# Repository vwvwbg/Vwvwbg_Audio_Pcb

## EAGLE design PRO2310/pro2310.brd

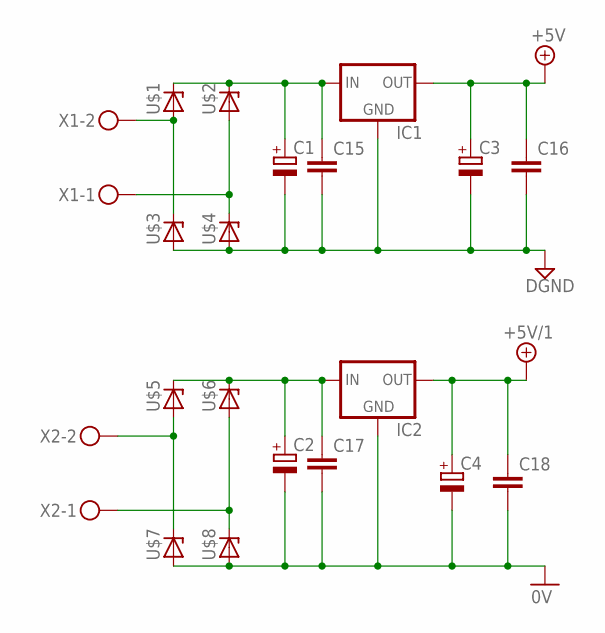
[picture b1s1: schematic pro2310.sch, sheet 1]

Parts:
C1, C2: CPOL-EUE5-10.5; E5-10,5
C3, C4: CPOL-EUE3.5-8; E3,5-8
C15, C16, C17, C18: C-EU050-055X075; C050-055X075
IC1: 78LXX
IC2: 78MXXL
U$1, U$2, U$3, U$4, U$5, U$6, U$7, U$8: 1N4148-V; 1N4148
X1, X2: MKDSN1,5/2-5,08

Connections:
0V: C2.-, C4.-, C17.2, C18.2, IC2.GND, U$7.A, U$8.A; also elsewhere on the board
+5V: C3.+, C16.1, IC1.OUT; also elsewhere on the board
+5V/1: C4.+, C18.1, IC2.OUT; also elsewhere on the board
DGND: C1.-, C3.-, C15.2, C16.2, IC1.GND, U$3.A, U$4.A; also elsewhere on the board
unnamed: C1.+, C15.1, IC1.IN, U$1.C, U$2.C
unnamed: U$5.A, U$7.C, X2.2
unnamed: U$6.A, U$8.C, X2.1
unnamed: U$2.A, U$4.C, X1.1
unnamed: C2.+, C17.1, IC2.IN, U$5.C, U$6.C
unnamed: U$1.A, U$3.C, X1.2

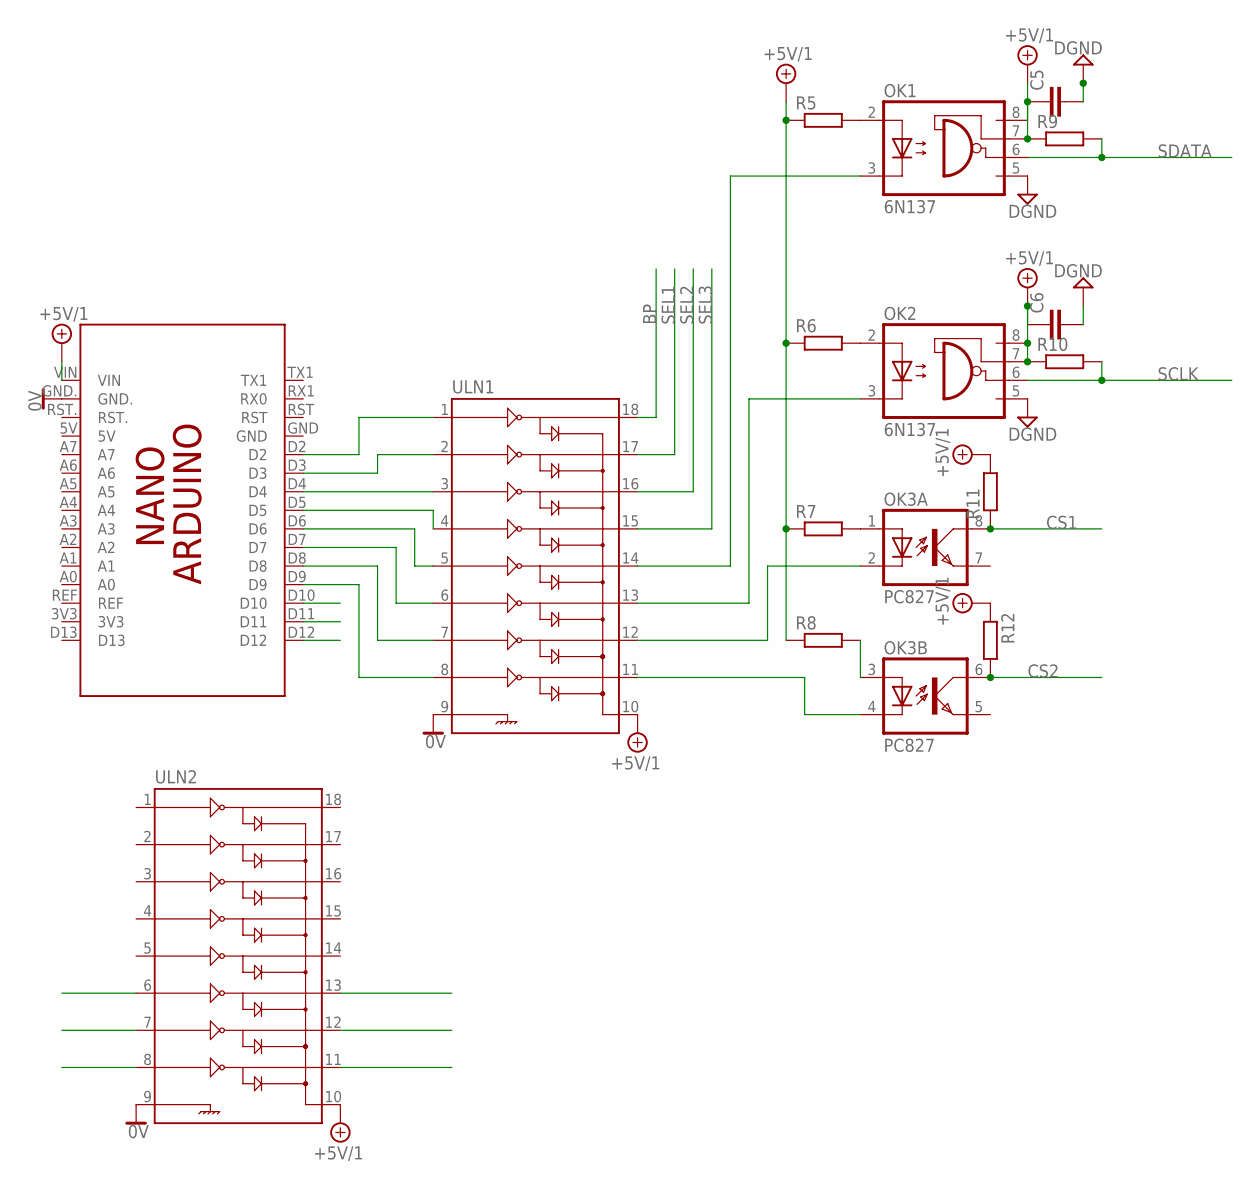
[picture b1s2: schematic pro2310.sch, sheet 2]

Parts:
C5, C6: C-EU025-025X050; C025-025X050
OK1, OK2: 6N137; DIL08
OK3: PC827; DIL08
PCB1: ARDUINO_NANO
R5, R6, R7, R8, R9, R10, R11, R12: R-EU_0207/2V; 0207/2V
ULN1, ULN2: ULN2803DIP; DIL18

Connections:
0V: PCB1.GND., ULN1.9, ULN2.9; also elsewhere on the board
+5V/1: C5.1, C6.1, OK1.7 (VE), OK1.8 (VCC), OK2.7 (VE), OK2.8 (VCC), PCB1.VIN, R5.1, R6.1, R7.1, R8.1, R9.1, R10.1, R11.2, R12.1, ULN1.10, ULN2.10; also elsewhere on the board
BP: ULN1.18; also elsewhere on the board
CS1: OK3.8 (COL), R11.1; also elsewhere on the board
CS2: OK3.6 (COL), R12.2; also elsewhere on the board
D2: PCB1.D2, ULN1.1
D3: PCB1.D3, ULN1.2
D4: PCB1.D4, ULN1.3
D5: PCB1.D5, ULN1.4
D6: PCB1.D6, ULN1.5
D7: PCB1.D7, ULN1.6
D8: PCB1.D8, ULN1.7
D9: PCB1.D9, ULN1.8
D10: PCB1.D10, ULN2.8
D11: PCB1.D11, ULN2.7
D12: PCB1.D12, ULN2.6
DGND: C5.2, C6.2, OK1.5 (GND), OK2.5 (GND); also elsewhere on the board
unnamed: OK1.2 (A), R5.2
unnamed: OK2.2 (A), R6.2
unnamed: OK3.1 (A), R7.2
unnamed: OK3.3 (A), R8.2
unnamed: OK1.3 (C), ULN1.14
unnamed: OK3.2 (C), ULN1.12
unnamed: OK3.4 (C), ULN1.11
unnamed: OK2.3 (C), ULN1.13
OUT1: ULN2.13; also elsewhere on the board
OUT2: ULN2.12; also elsewhere on the board
OUT3: ULN2.11; also elsewhere on the board
SCLK: OK2.6 (VO), R10.2; also elsewhere on the board
SDATA: OK1.6 (VO), R9.2; also elsewhere on the board
SEL1: ULN1.17; also elsewhere on the board
SEL2: ULN1.16; also elsewhere on the board
SEL3: ULN1.15; also elsewhere on the board

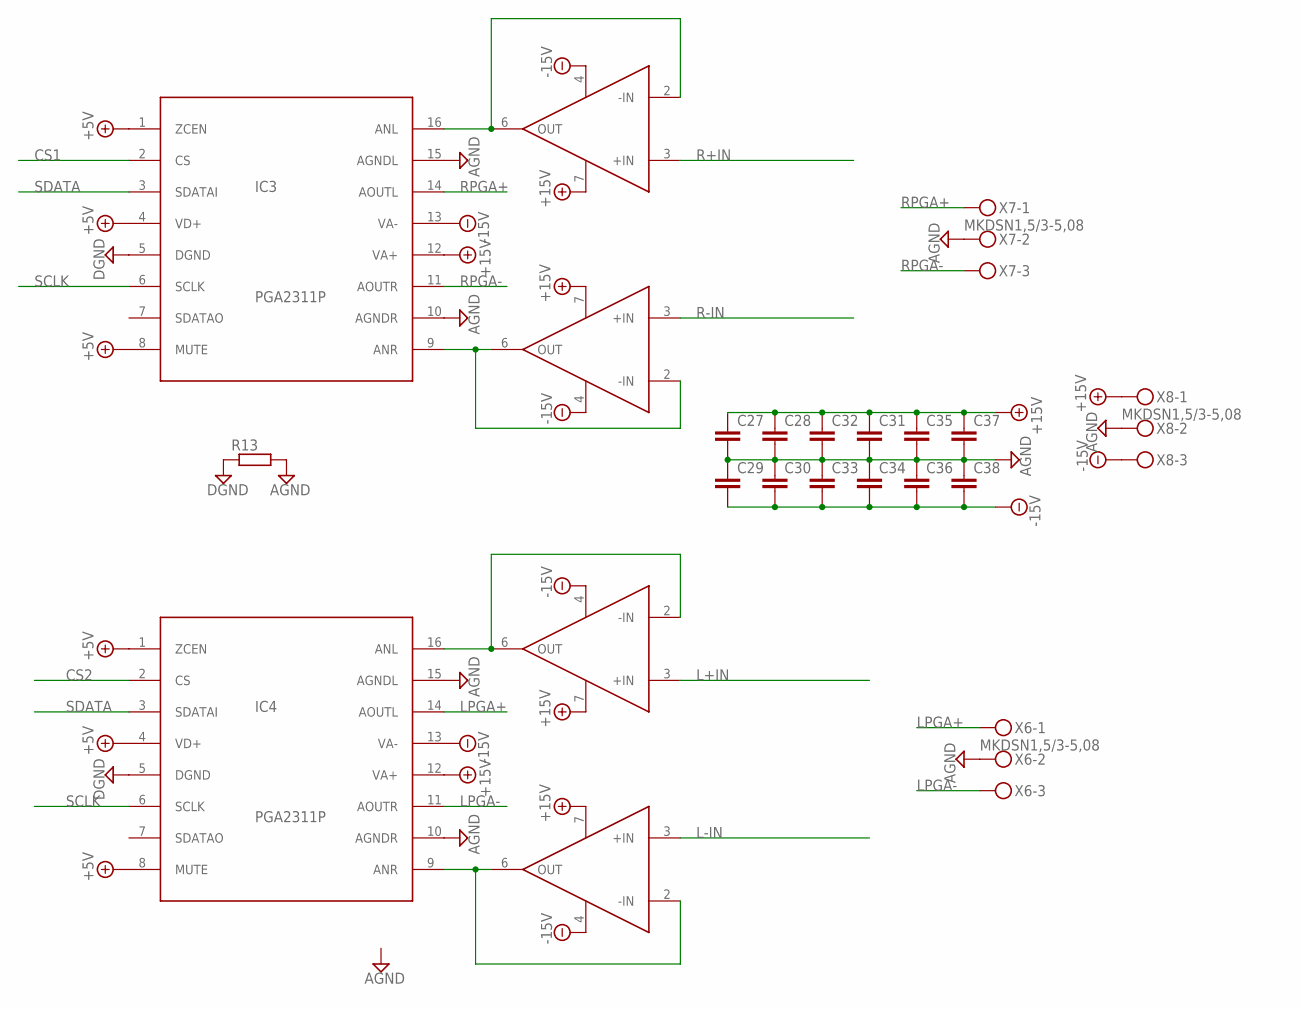
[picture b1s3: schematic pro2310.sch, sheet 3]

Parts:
C27, C28, C29, C30, C31, C32, C33, C34, C35, C36, C37, C38: C-EU025-025X050; C025-025X050
IC3, IC4: PGA2311P; DIL16
R13: R-EU_0207/7; 0207/7
U1, U2, U3, U4: OPA627BP; DIL08
X6, X7, X8: MKDSN1,5/3-5,08

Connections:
+5V: IC3.1 (ZCEN), IC3.4 (VD+), IC3.8 (MUTE), IC4.1 (ZCEN), IC4.4 (VD+), IC4.8 (MUTE); also elsewhere on the board
+15V: C27.1, C28.1, C31.1, C32.1, C35.1, C37.1, IC3.12 (VA+), IC4.12 (VA+), U1.7 (V+), U2.7 (V+), U3.7 (V+), U4.7 (V+), X8.1
-15V: C29.2, C30.2, C33.2, C34.2, C36.2, C38.2, IC3.13 (VA-), IC4.13 (VA-), U1.4 (V-), U2.4 (V-), U3.4 (V-), U4.4 (V-), X8.3
AGND: C27.2, C28.2, C29.1, C30.1, C31.2, C32.2, C33.1, C34.1, C35.2, C36.1, C37.2, C38.1, IC3.10 (AGNDR), IC3.15 (AGNDL), IC4.10 (AGNDR), IC4.15 (AGNDL), R13.2, X6.2, X7.2, X8.2; also elsewhere on the board
CS1: IC3.2 (CS); also elsewhere on the board
CS2: IC4.2 (CS); also elsewhere on the board
DGND: IC3.5 (DGND), IC4.5 (DGND), R13.1; also elsewhere on the board
L+IN: U3.3 (+IN); also elsewhere on the board
L-IN: U4.3 (+IN); also elsewhere on the board
LPGA+: IC4.14 (AOUTL), X6.1; also elsewhere on the board
LPGA-: IC4.11 (AOUTR), X6.3; also elsewhere on the board
unnamed: IC3.9 (ANR), U2.2 (-IN), U2.6 (OUT)
unnamed: IC3.16 (ANL), U1.2 (-IN), U1.6 (OUT)
unnamed: IC4.9 (ANR), U4.2 (-IN), U4.6 (OUT)
unnamed: IC4.16 (ANL), U3.2 (-IN), U3.6 (OUT)
R+IN: U1.3 (+IN); also elsewhere on the board
R-IN: U2.3 (+IN); also elsewhere on the board
RPGA+: IC3.14 (AOUTL), X7.1; also elsewhere on the board
RPGA-: IC3.11 (AOUTR), X7.3; also elsewhere on the board
SCLK: IC3.6 (SCLK), IC4.6 (SCLK); also elsewhere on the board
SDATA: IC3.3 (SDATAI), IC4.3 (SDATAI); also elsewhere on the board

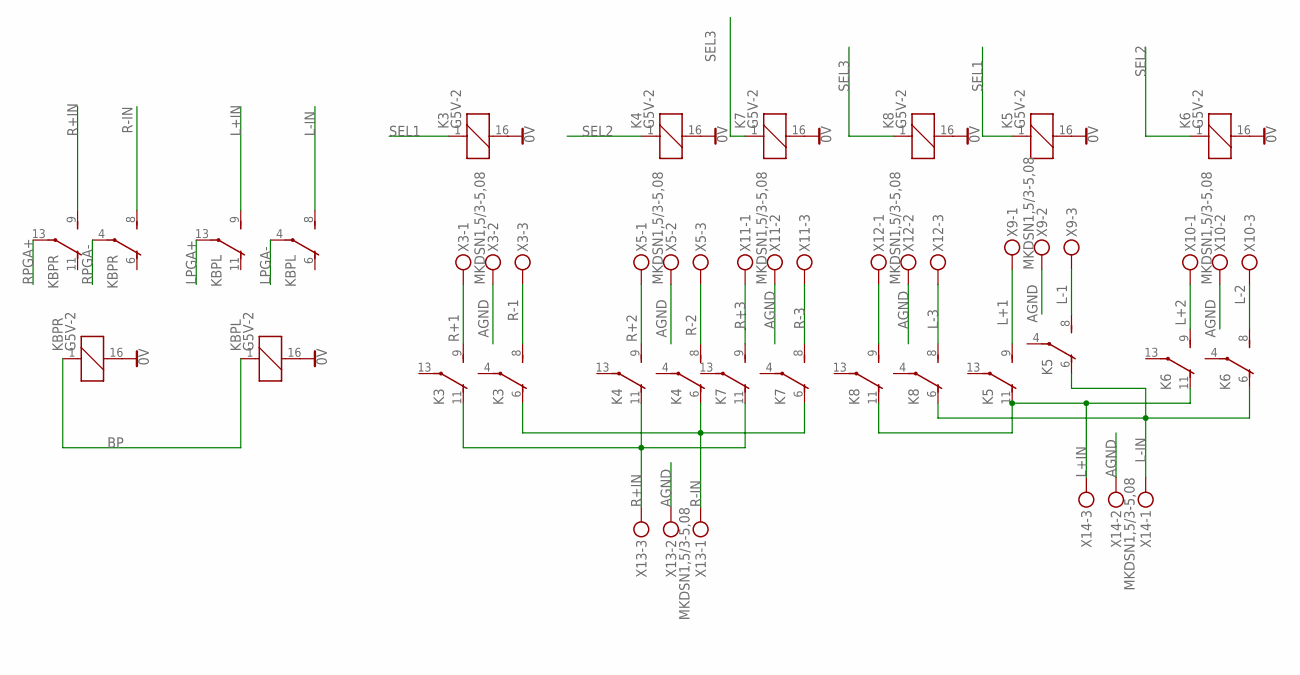
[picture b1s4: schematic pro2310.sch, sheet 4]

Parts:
K3, K4, K5, K6, K7, K8: G5V-2
KBPL: G5V-2
KBPR: G5V-2
X3, X5, X9, X10, X11, X12, X13, X14: MKDSN1,5/3-5,08

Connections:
0V: K3.16 (2), K4.16 (2), K5.16 (2), K6.16 (2), K7.16 (2), K8.16 (2), KBPL.16 (2), KBPR.16 (2); also elsewhere on the board
AGND: X3.2, X5.2, X9.2, X10.2, X11.2, X12.2, X13.2, X14.2; also elsewhere on the board
BP: KBPL.1, KBPR.1; also elsewhere on the board
L+1: K5.9 (S), X9.1
L+2: K6.9 (S), X10.1
L+3: K8.9 (S), X12.1
L+IN: K5.11 (O), K6.11 (O), K8.11 (O), KBPL.9 (S), X14.3; also elsewhere on the board
L-1: K5.8 (S), X9.3
L-2: K6.8 (S), X10.3
L-3: K8.8 (S), X12.3
L-IN: K5.6 (O), K6.6 (O), K8.6 (O), KBPL.8 (S), X14.1; also elsewhere on the board
LPGA+: KBPL.13; also elsewhere on the board
LPGA-: KBPL.4; also elsewhere on the board
R+1: K3.9 (S), X3.1
R+2: K4.9 (S), X5.1
R+3: K7.9 (S), X11.1
R+IN: K3.11 (O), K4.11 (O), K7.11 (O), KBPR.9 (S), X13.3; also elsewhere on the board
R-1: K3.8 (S), X3.3
R-2: K4.8 (S), X5.3
R-3: K7.8 (S), X11.3
R-IN: K3.6 (O), K4.6 (O), K7.6 (O), KBPR.8 (S), X13.1; also elsewhere on the board
RPGA+: KBPR.13; also elsewhere on the board
RPGA-: KBPR.4; also elsewhere on the board
SEL1: K3.1, K5.1; also elsewhere on the board
SEL2: K4.1, K6.1; also elsewhere on the board
SEL3: K7.1, K8.1; also elsewhere on the board

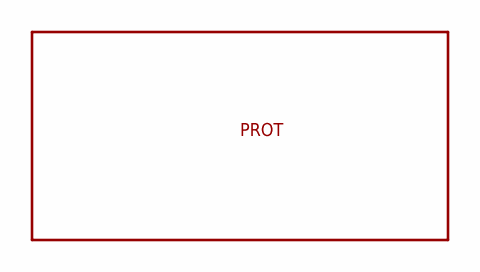
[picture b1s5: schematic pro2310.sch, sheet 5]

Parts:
U$15: PROT

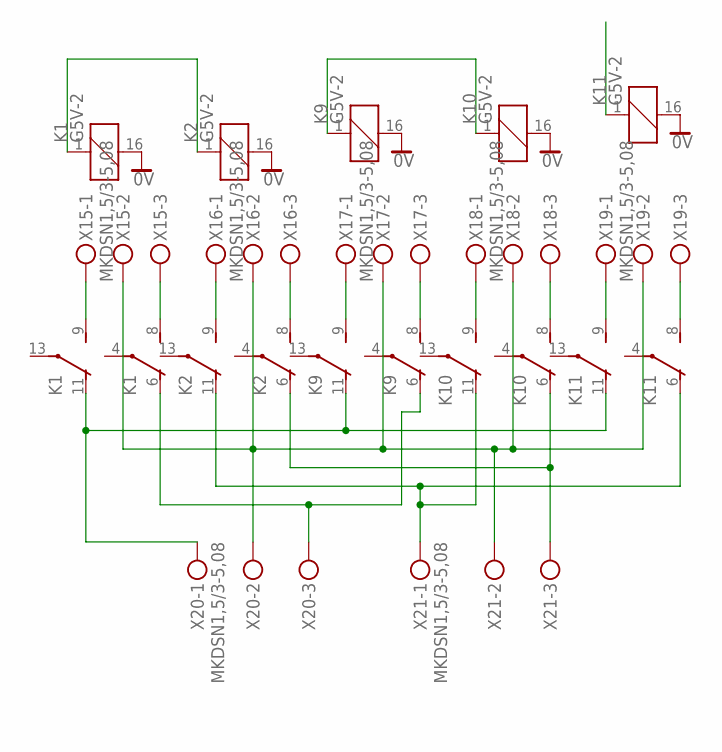
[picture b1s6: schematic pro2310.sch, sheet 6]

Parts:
K1, K2, K9, K10, K11: G5V-2
X15, X16, X17, X18, X19, X20, X21: MKDSN1,5/3-5,08

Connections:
0V: K1.16 (2), K2.16 (2), K9.16 (2), K10.16 (2), K11.16 (2); also elsewhere on the board
GOUT: X15.2, X16.2, X17.2, X18.2, X19.2, X20.2, X21.2
LOUT+: K2.11 (O), K10.11 (O), K11.6 (O), X21.1
LOUT-: K2.6 (O), K10.6 (O), X21.3
unnamed: K1.8 (S), X15.3
unnamed: K1.9 (S), X15.1
unnamed: K2.9 (S), X16.1
unnamed: K2.8 (S), X16.3
unnamed: K9.9 (S), X17.1
unnamed: K9.8 (S), X17.3
unnamed: K10.9 (S), X18.1
unnamed: K10.8 (S), X18.3
unnamed: K11.9 (S), X19.1
unnamed: K11.8 (S), X19.3
OUT1: K1.1, K2.1; also elsewhere on the board
OUT2: K9.1, K10.1; also elsewhere on the board
OUT3: K11.1; also elsewhere on the board
ROUT+: K1.11 (O), K9.11 (O), K11.11 (O), X20.1
ROUT-: K1.6 (O), K9.6 (O), X20.3

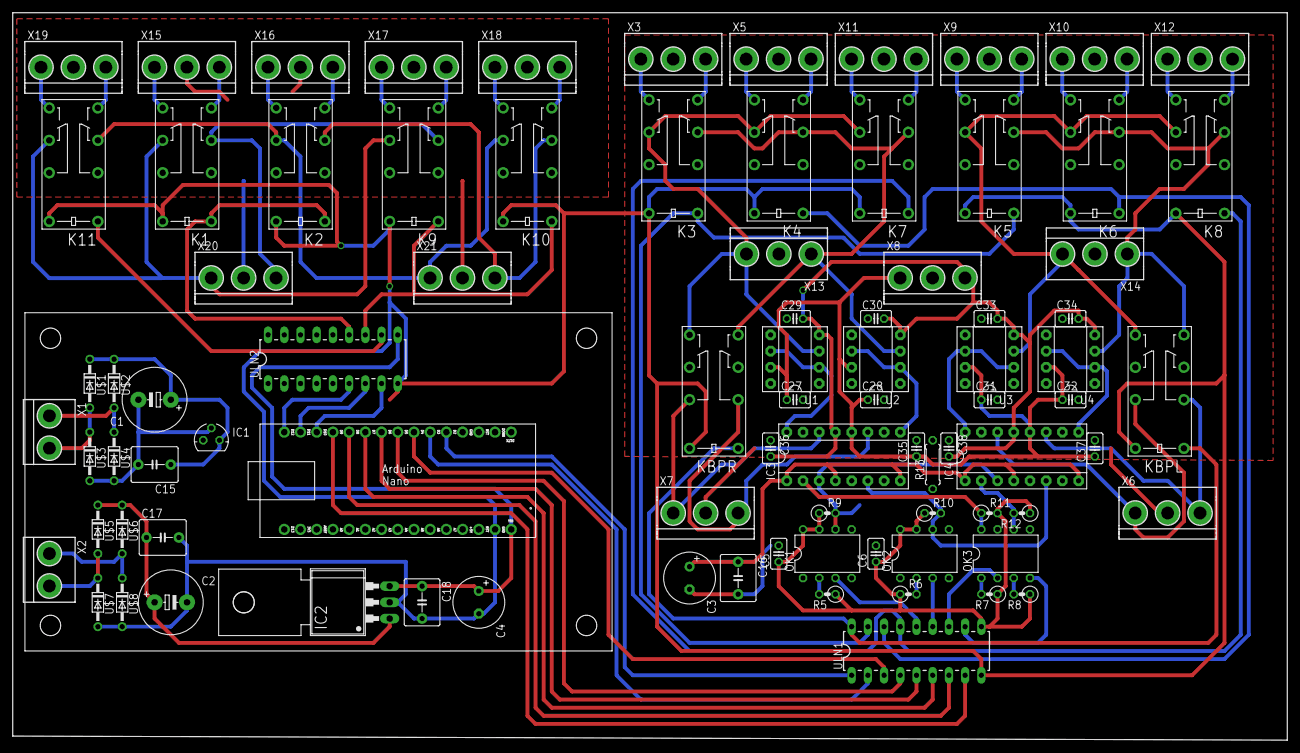
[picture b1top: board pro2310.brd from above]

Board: 2 copper layers, 199.7 x 114.0 mm, 87 parts (0 on the bottom side), 82 nets.

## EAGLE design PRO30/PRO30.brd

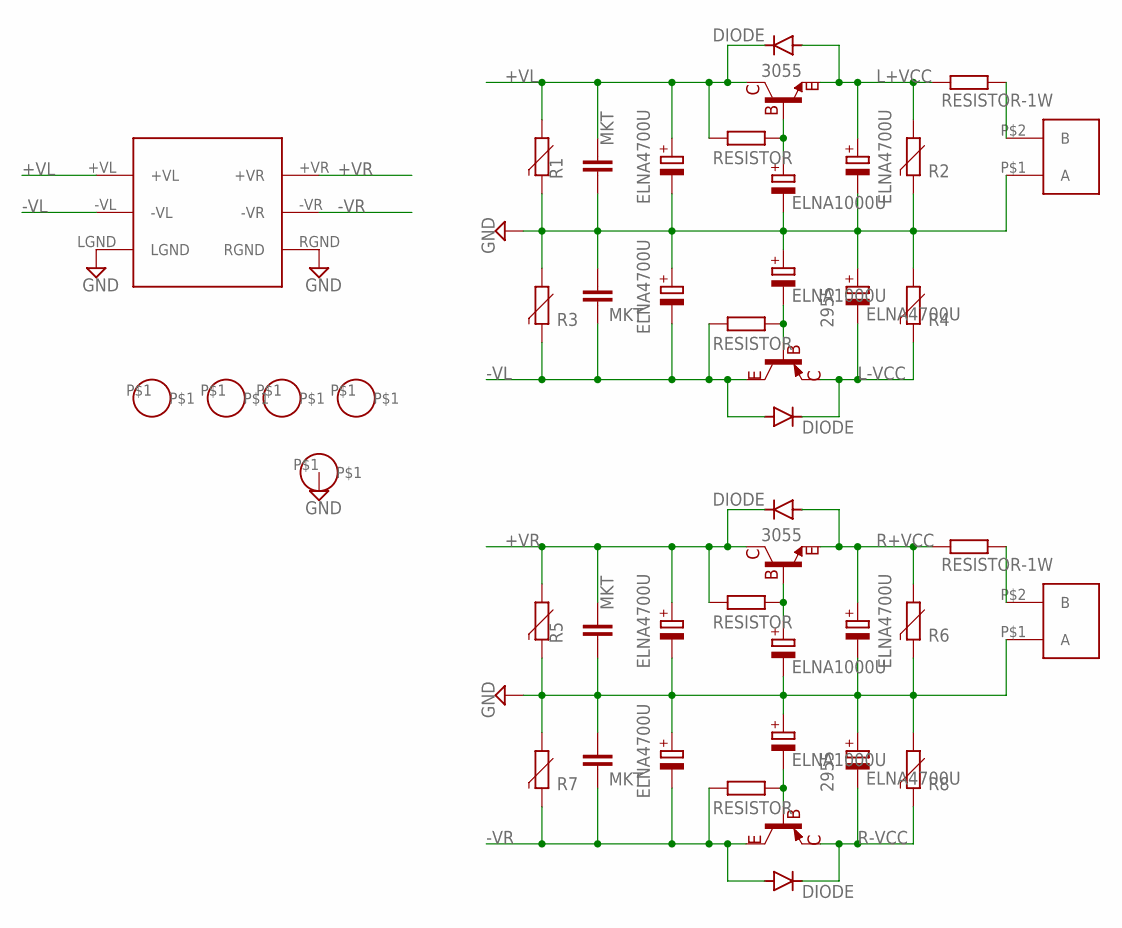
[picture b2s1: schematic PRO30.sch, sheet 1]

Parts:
R1, R2, R3, R4, R5, R6, R7, R8: NTC
U$1: INPUT
U$3, U$5, U$6, U$7, U$9, U$10, U$83, U$84: ELNA4700U; 4700U
U$12, U$16, U$85, U$86: ELNA1000U; 1000U
U$24, U$87: 2955; POWER_TRANS
U$26, U$88: 3055; POWER_TRANS
U$28, U$29, U$89, U$90: DIODE
U$30, U$34, U$91, U$92: MKT; NTC
U$40, U$43, U$93, U$96: RESISTOR
U$41, U$94: OUT2; OUT2"
U$42, U$95: RESISTOR-1W
U$101, U$102, U$106, U$107, U$108: HOLE

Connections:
+VL: R1.2, U$1.+VL, U$3.+, U$26.C, U$28.C, U$30.1, U$40.P$2 (2)
+VR: R5.2, U$1.+VR, U$9.+, U$88.C, U$89.C, U$91.1, U$93.P$2 (2)
-VL: R3.1, U$1.-VL, U$7.-, U$24.C, U$29.A, U$34.2, U$43.P$2 (2)
-VR: R7.1, U$1.-VR, U$84.-, U$87.C, U$90.A, U$92.2, U$96.P$2 (2)
GND: R1.1, R2.1, R3.2, R4.2, R5.1, R6.1, R7.2, R8.2, U$1.LGND, U$1.RGND, U$3.-, U$5.+, U$6.-, U$7.+, U$9.-, U$10.+, U$12.-, U$16.+, U$30.2, U$34.1, U$41.P$1 (A), U$83.-, U$84.+, U$85.-, U$86.+, U$91.2, U$92.1, U$94.P$1 (A), U$108.P$1; also elsewhere on the board
L+VCC: R2.2, U$6.+, U$26.E, U$28.A, U$42.P$1 (1); also elsewhere on the board
L-VCC: R4.1, U$5.-, U$24.E, U$29.C; also elsewhere on the board
unnamed: U$85.+, U$88.B, U$93.P$1 (1)
unnamed: U$12.+, U$26.B, U$40.P$1 (1)
unnamed: U$41.P$2 (B), U$42.P$2 (2)
unnamed: U$16.-, U$24.B, U$43.P$1 (1)
unnamed: U$94.P$2 (B), U$95.P$2 (2)
unnamed: U$86.-, U$87.B, U$96.P$1 (1)
R+VCC: R6.2, U$83.+, U$88.E, U$89.A, U$95.P$1 (1); also elsewhere on the board
R-VCC: R8.1, U$10.-, U$87.E, U$90.C; also elsewhere on the board

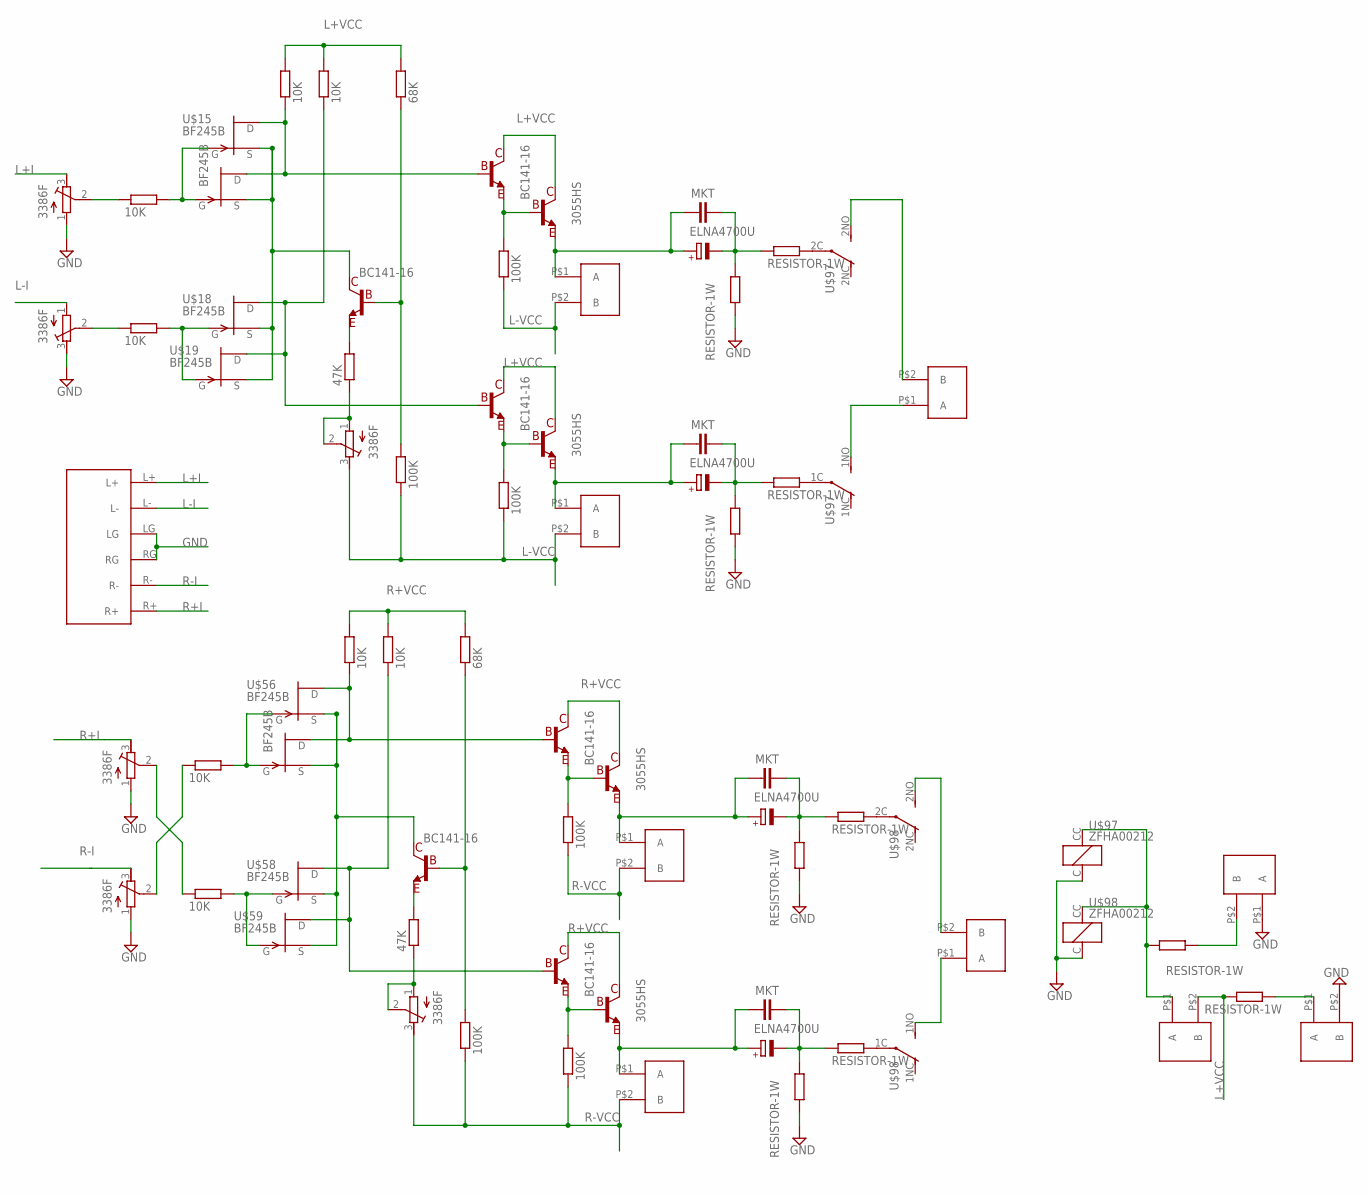
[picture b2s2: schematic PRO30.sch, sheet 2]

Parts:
DN>L: OUT2; OUT2"
DP_SW: OUT2; OUT2"
U$2: AUDIO_INPUT
U$4, U$8, U$31, U$52, U$53, U$63: 3386F; 3386
U$11, U$20, U$21, U$25, U$54, U$60, U$81, U$82: 10K; RESISTOR
U$13, U$80: 68K; RESISTOR
U$14, U$22, U$23, U$55, U$61, U$70: BC141-16; TO39
U$15, U$17, U$18, U$19, U$56, U$57, U$58, U$59: BF245B; TO39
U$27, U$62: 47K; RESISTOR
U$32, U$33, U$64, U$71: 3055HS; POWER_TRANS_WHS
U$35, U$44, U$65, U$72, U$104, U$105: OUT3; OUT3"
U$36, U$45, U$66, U$73: ELNA4700U; 4700U
U$37, U$46, U$67, U$74: MKT; NTC
U$38, U$39, U$47, U$48, U$68, U$69, U$75, U$76, U$99, U$100: RESISTOR-1W
U$49, U$50, U$51, U$77, U$78, U$79: 100K; RESISTOR
U$97, U$98: ZFHA00212; ZFHA002
U$103: OUT2; OUT2"

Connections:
GND: DN>L.P$2 (B), U$2.LG, U$2.RG, U$4.1, U$8.3, U$38.P$1 (1), U$47.P$1 (1), U$52.1, U$53.1, U$68.P$1 (1), U$75.P$1 (1), U$97.C, U$98.C, U$103.P$1 (A); also elsewhere on the board
L+I: U$2.L+, U$4.3
L+VCC: DP_SW.P$2 (B), U$13.P$2 (2), U$20.P$2 (2), U$22.C/G (C), U$23.C/G (C), U$25.P$2 (2), U$32.C, U$33.C, U$99.P$2 (2); also elsewhere on the board
L-I: U$2.L-, U$8.1
L-VCC: U$31.3, U$35.P$2 (B), U$44.P$2 (B), U$49.P$1 (1), U$50.P$1 (1), U$51.P$1 (1); also elsewhere on the board
unnamed: U$4.2, U$11.P$1 (1)
unnamed: U$11.P$2 (2), U$15.C/G (G), U$17.C/G (G)
unnamed: U$15.E/D (D), U$17.E/D (D), U$22.B/S (B), U$25.P$1 (1)
unnamed: U$14.C/G (C), U$15.B/S (S), U$17.B/S (S), U$18.B/S (S), U$19.B/S (S)
unnamed: U$13.P$1 (1), U$14.B/S (B), U$49.P$2 (2)
unnamed: U$8.2, U$21.P$1 (1)
unnamed: U$18.C/G (G), U$19.C/G (G), U$21.P$2 (2)
unnamed: U$52.2, U$60.P$1 (1)
unnamed: U$54.P$2 (2), U$56.C/G (G), U$57.C/G (G)
unnamed: U$14.E/D (E), U$27.P$2 (2)
unnamed: U$27.P$1 (1), U$31.1, U$31.2
unnamed: U$22.E/D (E), U$33.B, U$51.P$2 (2)
unnamed: U$18.E/D (D), U$19.E/D (D), U$20.P$1 (1), U$23.B/S (B)
unnamed: U$32.E, U$44.P$1 (A), U$45.+, U$46.1
unnamed: U$33.E, U$35.P$1 (A), U$36.+, U$37.1
unnamed: U$36.-, U$37.2, U$38.P$2 (2), U$39.P$1 (1)
unnamed: U$45.-, U$46.2, U$47.P$2 (2), U$48.P$1 (1)
unnamed: U$56.E/D (D), U$57.E/D (D), U$61.B/S (B), U$82.P$1 (1)
unnamed: U$23.E/D (E), U$32.B, U$50.P$2 (2)
unnamed: U$55.C/G (C), U$56.B/S (S), U$57.B/S (S), U$58.B/S (S), U$59.B/S (S)
unnamed: U$58.C/G (G), U$59.C/G (G), U$60.P$2 (2)
unnamed: U$53.2, U$54.P$1 (1)
unnamed: U$55.E/D (E), U$62.P$2 (2)
unnamed: U$62.P$1 (1), U$63.1, U$63.2
unnamed: U$64.E, U$65.P$1 (A), U$66.+, U$67.1
unnamed: U$66.-, U$67.2, U$68.P$2 (2), U$69.P$1 (1)
unnamed: U$61.E/D (E), U$64.B, U$79.P$2 (2)
unnamed: U$58.E/D (D), U$59.E/D (D), U$70.B/S (B), U$81.P$1 (1)
unnamed: U$71.E, U$72.P$1 (A), U$73.+, U$74.1
unnamed: U$73.-, U$74.2, U$75.P$2 (2), U$76.P$1 (1)
unnamed: U$70.E/D (E), U$71.B, U$78.P$2 (2)
unnamed: U$55.B/S (B), U$77.P$2 (2), U$80.P$1 (1)
unnamed: U$48.P$2 (2), U$97.1C (C)
unnamed: U$39.P$2 (2), U$97.2C (C)
unnamed: U$97.1NO (NO), U$104.P$1 (A)
unnamed: U$97.2NO (NO), U$104.P$2 (B)
unnamed: U$76.P$2 (2), U$98.1C (C)
unnamed: U$69.P$2 (2), U$98.2C (C)
unnamed: U$98.2NO (NO), U$105.P$2 (B)
unnamed: U$98.1NO (NO), U$105.P$1 (A)
unnamed: DP_SW.P$1 (A), U$97.CC (CT), U$98.CC (CT), U$100.P$2 (2)
unnamed: U$100.P$1 (1), U$103.P$2 (B)
unnamed: DN>L.P$1 (A), U$99.P$1 (1)
R+I: U$2.R+, U$52.3
R+VCC: U$61.C/G (C), U$64.C, U$70.C/G (C), U$71.C, U$80.P$2 (2), U$81.P$2 (2), U$82.P$2 (2); also elsewhere on the board
R-I: U$2.R-, U$53.3
R-VCC: U$63.3, U$65.P$2 (B), U$72.P$2 (B), U$77.P$1 (1), U$78.P$1 (1), U$79.P$1 (1); also elsewhere on the board

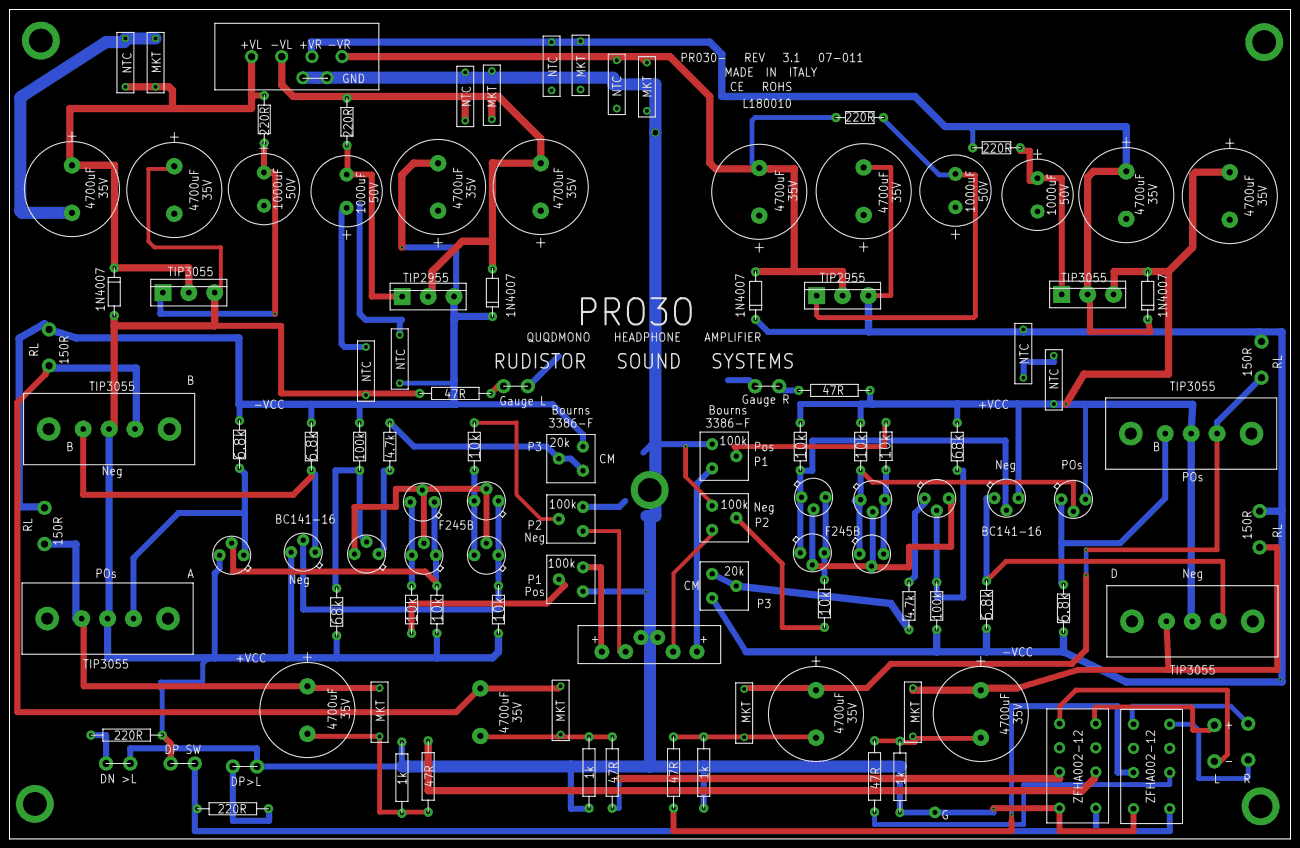
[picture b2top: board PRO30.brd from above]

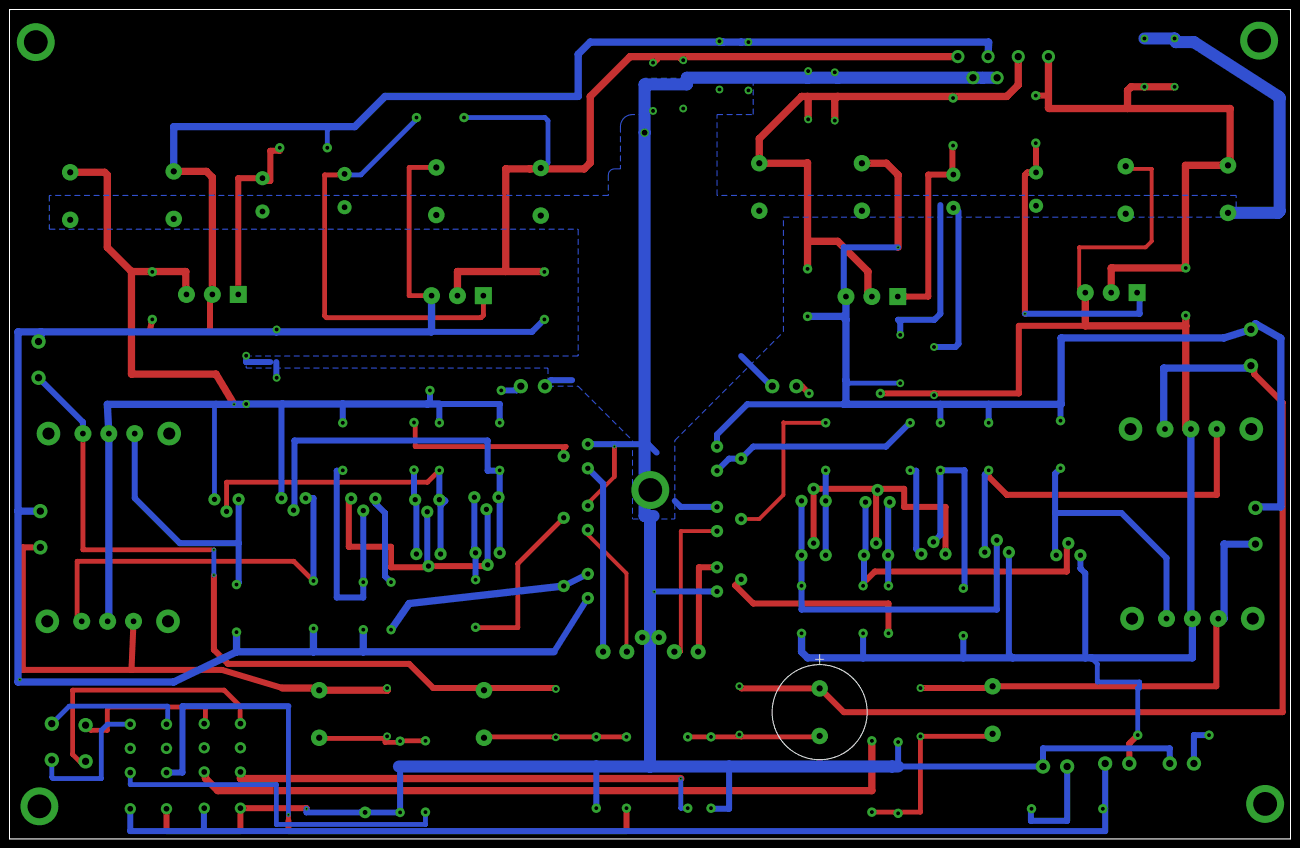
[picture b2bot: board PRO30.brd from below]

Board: 2 copper layers, 269.5 x 174.5 mm, 118 parts (2 on the bottom side), 62 nets.

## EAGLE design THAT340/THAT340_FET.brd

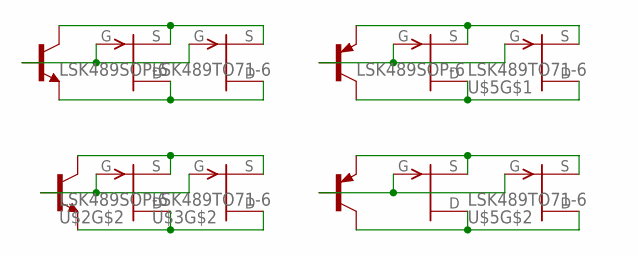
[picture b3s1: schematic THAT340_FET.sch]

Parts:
U$1: TRANSISTOR-ARRAYS_THAT340; TRANSISTOR-ARRAYS_DIP254P762X510-14
U$2, U$4: LSK489SOP-6; SOT-23-6
U$3, U$5: LSK489TO71-6; TO71-6

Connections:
unnamed: U$1.10 (E), U$4.6 (S), U$5.5 (S)
unnamed: U$1.8 (C), U$4.5 (D), U$5.6 (D)
unnamed: U$1.9 (B), U$4.4 (G), U$5.7 (G)
unnamed: U$1.7 (C), U$4.2 (D), U$5.2 (D)
unnamed: U$1.5 (E), U$4.3 (S), U$5.1 (S)
unnamed: U$1.6 (B), U$4.1 (G), U$5.3 (G)
unnamed: U$1.1 (C), U$2.3 (S), U$3.1 (S)
unnamed: U$1.3 (E), U$2.2 (D), U$3.2 (D)
unnamed: U$1.2 (B), U$2.1 (G), U$3.3 (G)
unnamed: U$1.13 (B), U$2.4 (G), U$3.7 (G)
unnamed: U$1.14 (C), U$2.6 (S), U$3.5 (S)
unnamed: U$1.12 (E), U$2.5 (D), U$3.6 (D)

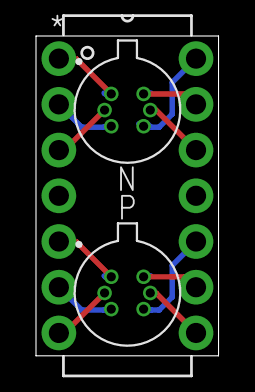
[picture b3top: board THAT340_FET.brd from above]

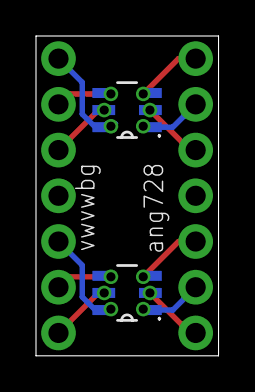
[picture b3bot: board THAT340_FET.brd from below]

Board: 2 copper layers, 10.1 x 17.8 mm, 5 parts (2 on the bottom side), 12 nets.

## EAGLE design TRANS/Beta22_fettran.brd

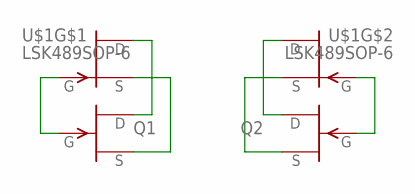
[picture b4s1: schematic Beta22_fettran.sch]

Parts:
Q1, Q2: 2SK170; TO92-
U$1: LSK489SOP-6; SOT-23-6

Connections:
unnamed: Q1.2 (G), U$1.1 (G)
unnamed: Q1.3 (S), U$1.3 (S)
unnamed: Q1.1 (D), U$1.2 (D)
unnamed: Q2.1 (D), U$1.5 (D)
unnamed: Q2.3 (S), U$1.6 (S)
unnamed: Q2.2 (G), U$1.4 (G)

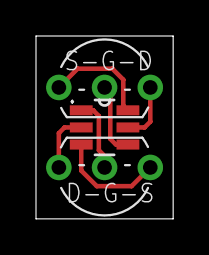
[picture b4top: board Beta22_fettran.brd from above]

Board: 2 copper layers, 7.6 x 10.2 mm, 3 parts (0 on the bottom side), 6 nets.

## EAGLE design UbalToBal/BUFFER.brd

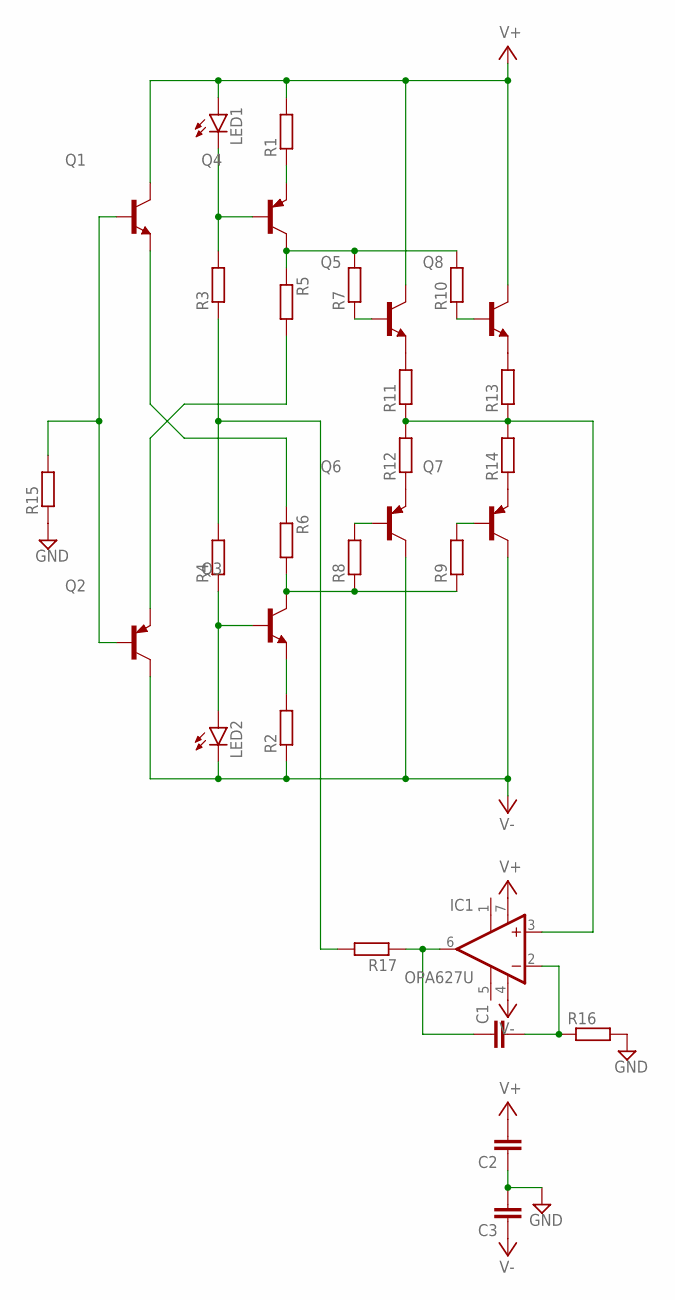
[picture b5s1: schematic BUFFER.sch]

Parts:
C1, C2, C3: C-EUC0805; C0805
IC1: OPA627U; SO08
LED1, LED2: LEDCHIPLED_1206; CHIPLED_1206
Q1, Q3, Q5, Q8: TRANSISTOR_BC846-NPN-SOT23-BEC; TRANSISTOR_SOT23-BEC
Q2, Q4, Q6, Q7: TRANSISTOR_BC856B-PNP-SOT23-BEC; TRANSISTOR_SOT23-BEC
R1, R2, R3, R4, R5, R6, R7, R8, R9, R10, R11, R12, R13, R14, R15, R16, R17: R-EU_MELF0204R; MINI_MELF-0204R

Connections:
GND: C2.1, C3.2, R15.1, R16.2
unnamed: Q1.B, Q2.B, R15.2
unnamed: Q2.E, R5.2
unnamed: Q3.E, R2.2
unnamed: Q4.E, R1.1
unnamed: LED1.C, Q4.B, R3.2
unnamed: LED2.A, Q3.B, R4.1
unnamed: Q4.C, R5.1, R7.2, R10.2
unnamed: Q3.C, R6.2, R8.1, R9.1
unnamed: Q1.E, R6.1
unnamed: R3.1, R4.2, R17.2
unnamed: Q5.B, R7.1
unnamed: Q5.E, R11.2
unnamed: Q7.B, R9.2
unnamed: Q8.B, R10.1
unnamed: Q6.B, R8.2
unnamed: Q6.E, R12.1
unnamed: IC1.3 (+IN), R11.1, R12.2, R13.1, R14.2
unnamed: Q8.E, R13.2
unnamed: Q7.E, R14.1
unnamed: C1.1, IC1.6 (OUT), R17.1
unnamed: C1.2, IC1.2 (-IN), R16.1
V+: C2.2, IC1.7 (V+), LED1.A, Q1.C, Q5.C, Q8.C, R1.2
V-: C3.1, IC1.4 (V-), LED2.C, Q2.C, Q6.C, Q7.C, R2.1

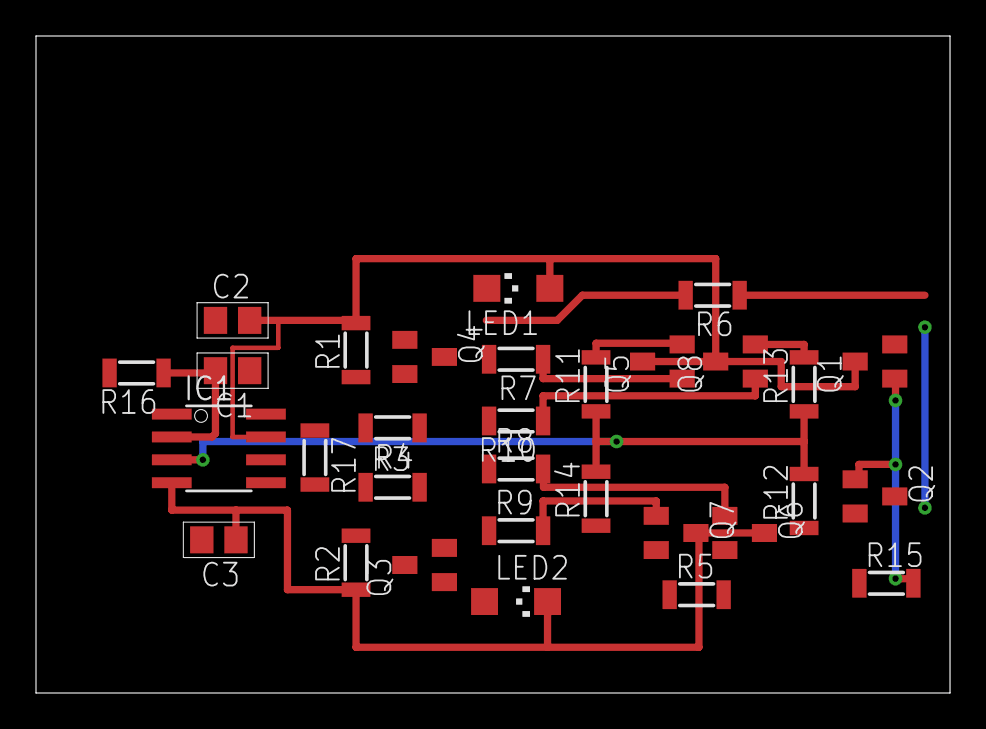
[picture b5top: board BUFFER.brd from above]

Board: 2 copper layers, 50.8 x 36.5 mm, 31 parts (0 on the bottom side), 24 nets.

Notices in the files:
parts and their libraries:
SparkFun-PowerIC: Licensing: Creative Commons ShareAlike 4.0 International - https://creativecommons.org/licenses/by-sa/4.0
